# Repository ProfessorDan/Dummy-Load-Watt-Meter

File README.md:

# Dummy-Load-Watt-Meter
Enhanced version of November QST Dummy Load meter adding dual range auto range Battery voltage

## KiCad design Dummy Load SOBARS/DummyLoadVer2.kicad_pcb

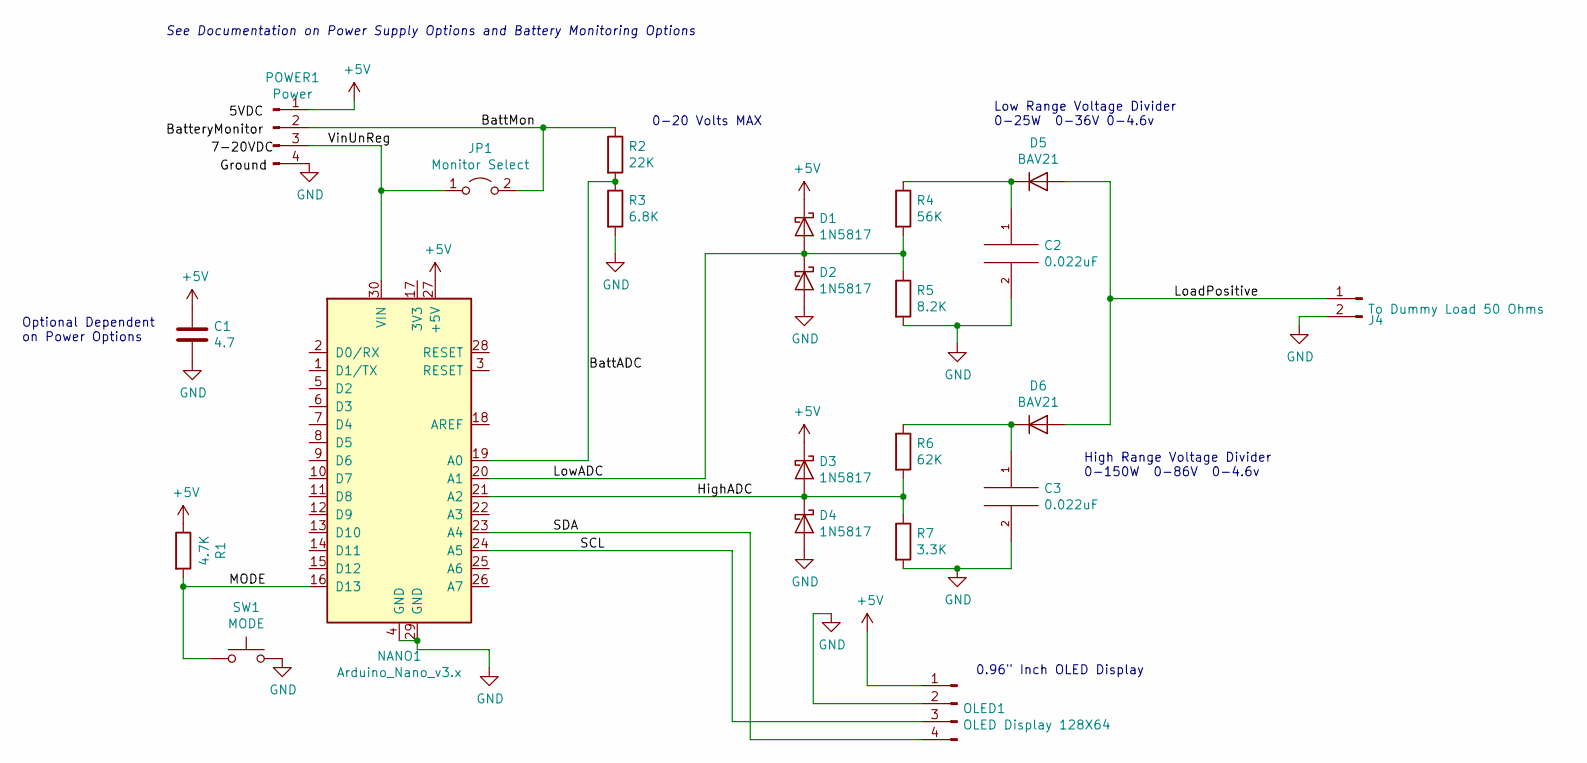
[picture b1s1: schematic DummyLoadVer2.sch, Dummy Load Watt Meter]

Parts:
C1: 4.7; CP_Radial_D5.0mm_P2.00mm
C2, C3: 0.022uF; C_Rect_L9.0mm_W4.2mm_P7.50mm_MKT
D1, D2, D3, D4: 1N5817; D_A-405_P7.62mm_Horizontal
D5, D6: BAV21; D_A-405_P7.62mm_Horizontal
J4: To Dummy Load 50 Ohms; SolderWirePad_1x02_P7.62mm_Drill2.5mm
JP1: Monitor Select; PinSocket_1x02_P2.54mm_Vertical
NANO1: Arduino_Nano_v3.x; Arduino_Nano
OLED1: OLED Display 128X64; PinSocket_1x04_P2.54mm_Vertical
POWER1: Power; PinHeader_1x04_P2.54mm_Vertical
R1: 4.7K; R_Axial_DIN0207_L6.3mm_D2.5mm_P10.16mm_Horizontal
R2: 22K; R_Axial_DIN0207_L6.3mm_D2.5mm_P10.16mm_Horizontal
R3: 6.8K; R_Axial_DIN0207_L6.3mm_D2.5mm_P10.16mm_Horizontal
R4: 56K; R_Axial_DIN0207_L6.3mm_D2.5mm_P10.16mm_Horizontal
R5: 8.2K; R_Axial_DIN0207_L6.3mm_D2.5mm_P10.16mm_Horizontal
R6: 62K; R_Axial_DIN0207_L6.3mm_D2.5mm_P10.16mm_Horizontal
R7: 3.3K; R_Axial_DIN0207_L6.3mm_D2.5mm_P10.16mm_Horizontal
SW1: MODE; SW_PUSH_6mm

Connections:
+5V: C1.1, D1.1 (K), D3.1 (K), NANO1.27 (+5V), OLED1.1, POWER1.1, R1.1
/BattADC: NANO1.19 (A0), R2.2, R3.1
/BattMon: JP1.2 (B), POWER1.2, R2.1
/HighADC: D3.2 (A), D4.1 (K), NANO1.21 (A2), R6.2, R7.1
/LoadPositive: D5.2 (A), D6.2 (A), J4.1
/LowADC: D1.2 (A), D2.1 (K), NANO1.20 (A1), R4.2, R5.1
/MODE: NANO1.16 (D13), R1.2, SW1.1
/SCL: NANO1.24 (A5), OLED1.3
/SDA: NANO1.23 (A4), OLED1.4
/VinUnReg: JP1.1 (A), NANO1.30 (VIN), POWER1.3
GND: C1.2, C2.2, C3.2, D2.2 (A), D4.2 (A), J4.2, NANO1.4 (GND), NANO1.29 (GND), OLED1.2, POWER1.4, R3.2, R5.2, R7.2, SW1.2
unnamed: C2.1, D5.1 (K), R4.1
unnamed: C3.1, D6.1 (K), R6.1

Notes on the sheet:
See Documentation on Power Supply Options and Battery Monitoring Options
Low Range Voltage Divider 0-25W 0-36V 0-4.6v
High Range Voltage Divider 0-150W 0-86V 0-4.6v
0-20 Volts MAX
0.96" Inch OLED Display
Optional Dependent on Power Options

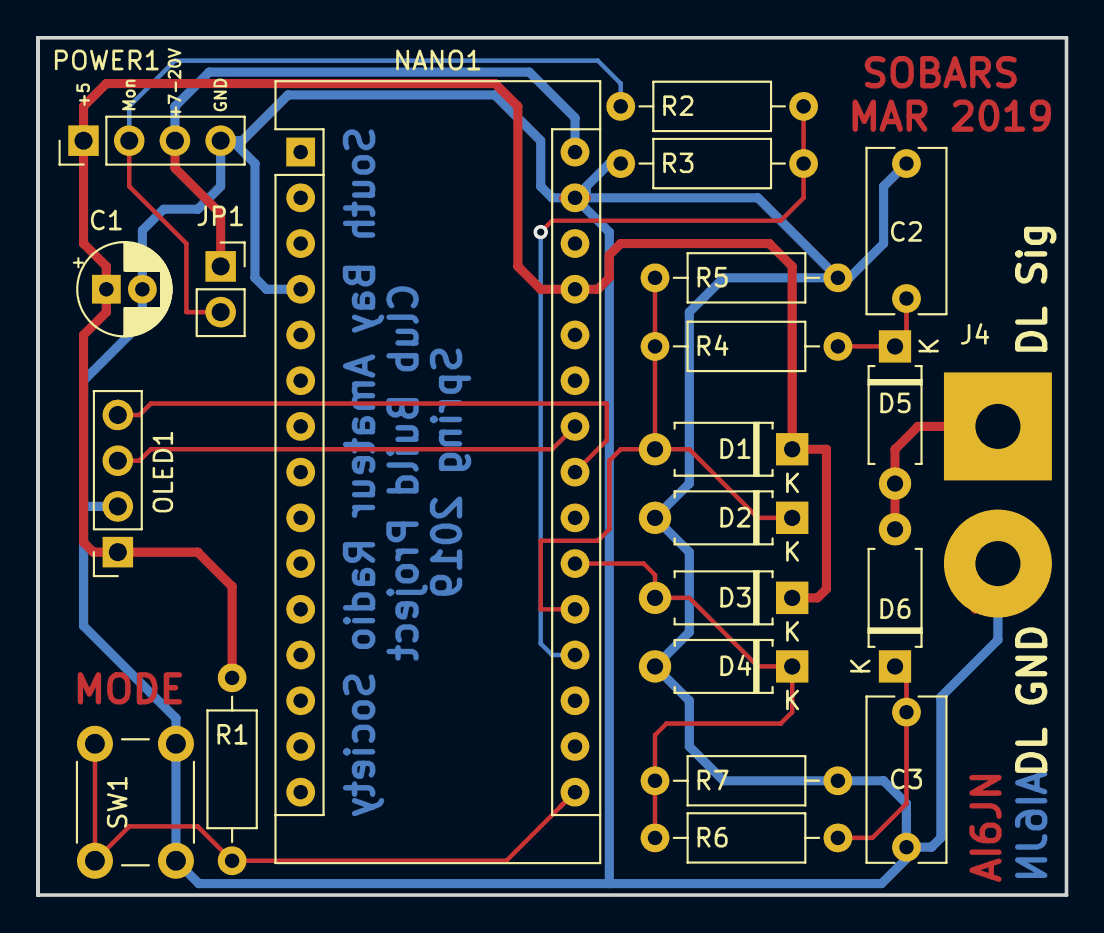
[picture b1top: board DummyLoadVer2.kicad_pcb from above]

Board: 2 copper layers, 57.2 x 47.6 mm, 22 parts (0 on the bottom side), 13 nets.

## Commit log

2019-01-14 KiCAD Project Files
    This contains the Schematics and PCB Design for the SOBARS Spring Build Project
2019-01-16 Working copy
    inwork
2019-02-11 Fix Mode Pin Digital Minor adjustments
    Clean up some traces
2019-03-04 Basic Working Version low range demo mode
    Demo
